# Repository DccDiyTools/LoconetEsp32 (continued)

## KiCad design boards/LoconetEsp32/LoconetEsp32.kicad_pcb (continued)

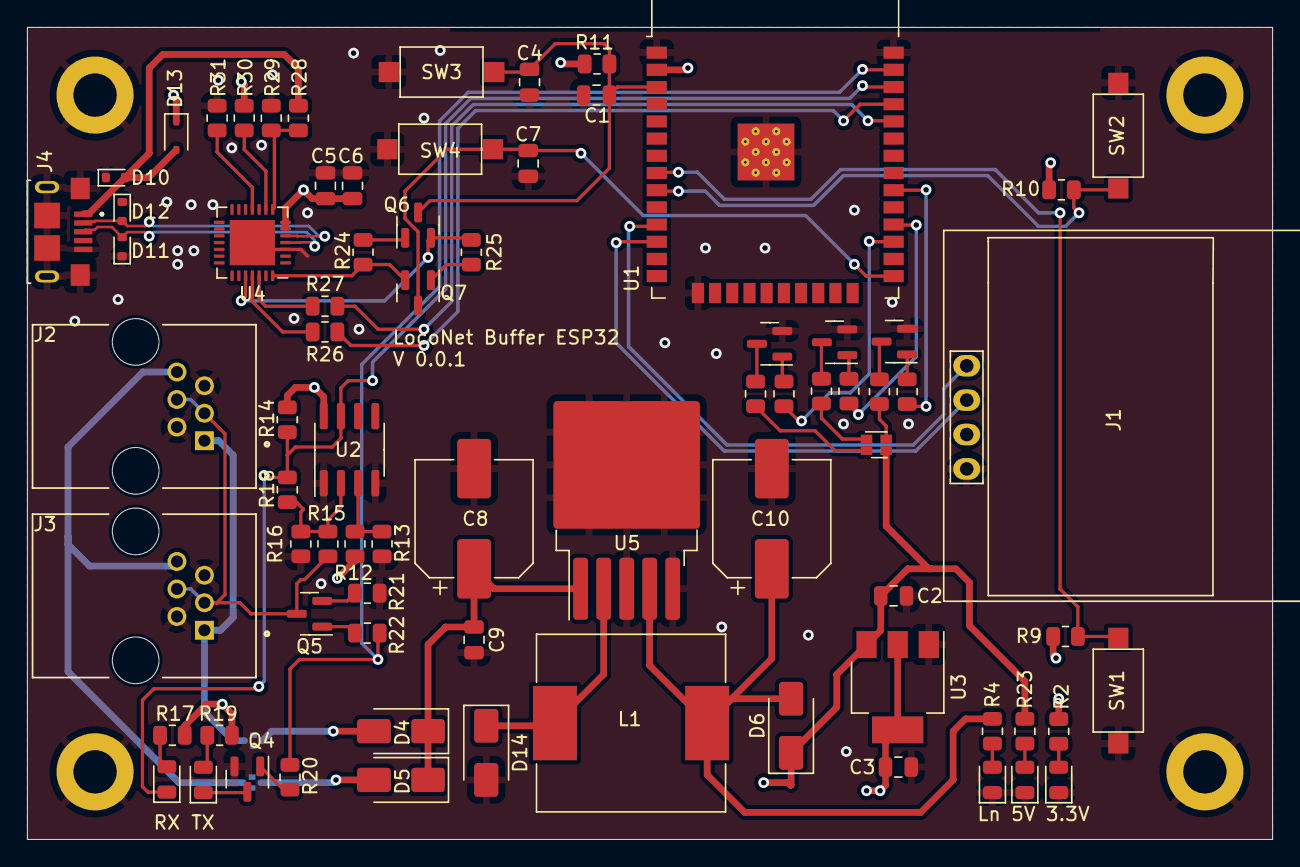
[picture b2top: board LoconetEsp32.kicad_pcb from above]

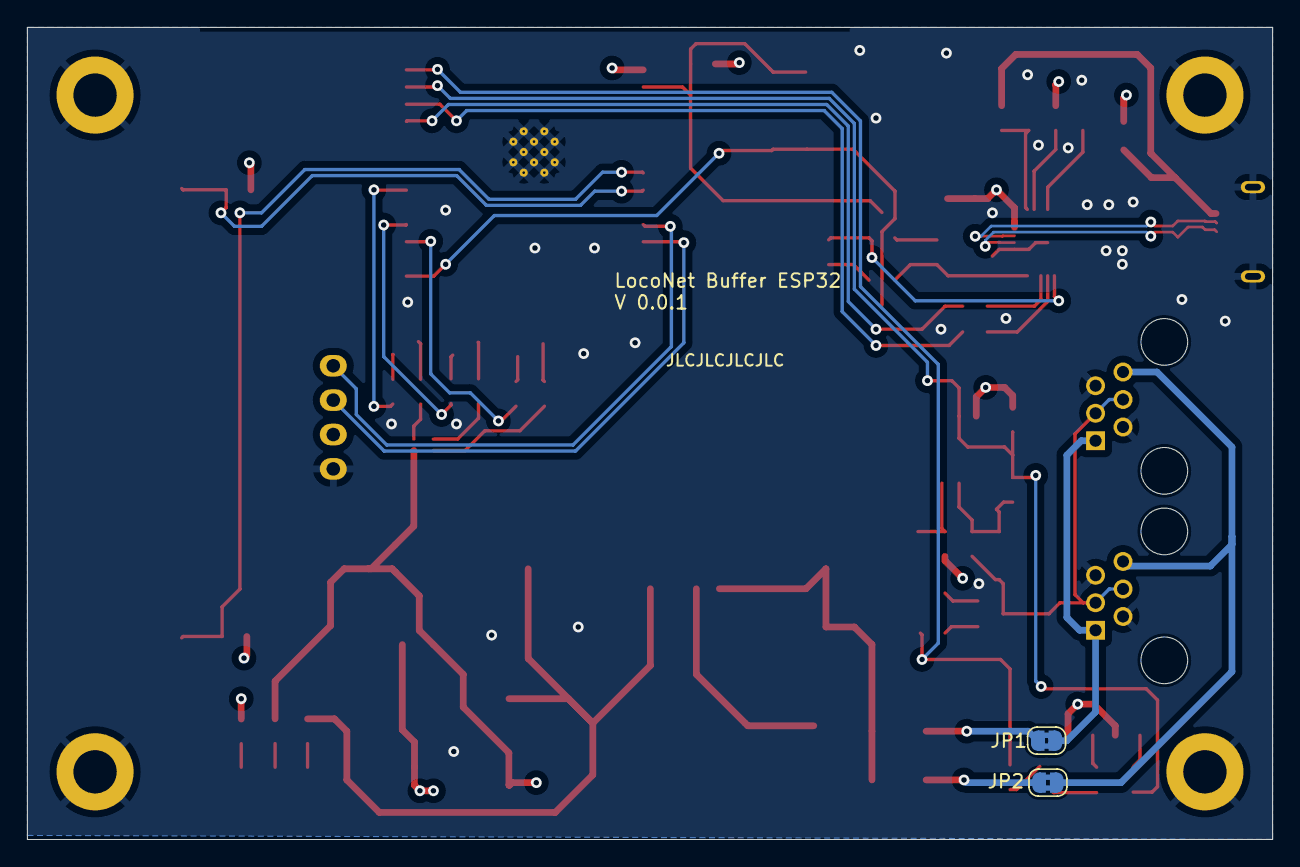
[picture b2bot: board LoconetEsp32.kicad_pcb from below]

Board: 4 copper layers, 92.0 x 60.0 mm, 82 parts (2 on the bottom side), 56 nets.

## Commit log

2024-04-30 Import From original Repo
2024-04-30 Import Docs from original Repo
2024-04-30 Import of Boards
2024-04-30 Change name to match folder
2024-05-07 Updated to kicad 8
2026-06-20 Update a Kicad 10 y eliminacion ERC
2026-06-20 Update PCB
2026-06-20 Docu Kibot 10
2026-06-20 Test Manual
2026-06-20 Otros DS
